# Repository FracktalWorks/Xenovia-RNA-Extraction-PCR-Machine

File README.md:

# Xenovia RT-PCR Machine

Ankit Bhatnagar
ankit.bhatnagarindia@gmail.com

Vijay Raghav Varada
vjvarada@fracktal.in

## Firmware Architecture

## Firmware Functional Block Diagram

* `main_window` in main.py is an object of `MainUI` class that is the workhorse for the firmware.
* `MainUI` class is the main workhorse. Using getter methods the `Printer` class and `Tests` class is parsed into the `MainUI` class. `xenovia.ui` is inherited by `MainUI` class.
* `xenovia_ui` is the generated code from the `xenovia_ui.ui` file made in Qt Designer and then converted into python code using PyQt5 UI code generator 5.14.2 .
* `Printer` class abstracts the Gcode calls to the control board connected over USB and presents an API that is used by `tests` and `MainUI` etc for printer movement functionality.
* `MKSCheck` creates the connection to the printer over USB.
* `MKSSerialCommunication` class handles the communication to the printer. It's initialised by the `Printer` class.
* `Tests` is the class that manages available tests, listing them, parsing their class object to `MainUI` etc.
* tests folder contains the assays which are dynamically initialised into `MainUI` by `Tests` class. Each Assay class inherits `TestBase` class.
* `TestBase` contains methods common to all Assays.
* When an assay class in dynamically created into `MainUI` by `Tests`, the base function movement classes of `Pipette`, `TipTrash`, `Magnet` etc which have motion related medhods are passed into it.
* `MechanicalParameters` has all the dimensions of the accessories in the machine, that the base function movement classes of `Pipette`, `TipTrash`, `Magnet` etc uses.

### Research Links:

## Xenovia Color Sensor 

### Main Components:
1. veml6040 colour sensor IC:  [Datasheet](https://www.vishay.com/docs/84276/veml6040.pdf)
2. TCA9548A I2C Switch: [Datasheet](https://www.ti.com/lit/ds/symlink/tca9548a.pdf)

### Research Links for interfacing:
1. Functionality and example application of TCA9548A [link](https://www.hackster.io/tarantula3/tca9548a-i2c-multiplexer-module-with-arduino-and-nodemcu-3d3313)
2. VEML6040 python example code [link](https://www.raspberrypi.org/forums/viewtopic.php?t=263498)
3. To test detection from raspberry pi and basic understanding of TCA9548A [link](https://www.raspberrypi.org/forums/viewtopic.php?t=146416)
4. Raspberry Pi I2C interfacing Tutorial, detecting connected hardware [link](https://learn.adafruit.com/adafruits-raspberry-pi-lesson-4-gpio-setup/configuring-i2c)
5. SMBus [link](http://wiki.erazor-zone.de/wiki:linux:python:smbus:doc)
### Degugging and Bugs:
#### Hardware:
V1.4
1. Upstream SDA SCL lines on the TCA9548A does not have pullup resistors, uses internal pullups on the raspberry pi board
2. Diodes on the Raspberry Pi shield need to be reversed due to error in placement from JLCPCB

#### Software:

1. Reset pin on Raspberry Pi is low by default, change to high to prevent resetting the TCA9548A or just disconnect the reset pin.

## Xenovia Application Auto Startup References

### X Server + Xenovia Application Autostart
1. https://www.raspberrypi.org/forums/viewtopic.php?t=42888
2. https://www.websences.com/dpkg-reconfigure-x11-common/
3. https://github.com/raspberrypi/linux/issues/2517#issuecomment-387867933

1. global xinitrc file : /etc/X11/xinit/xinitrc (set permissin a+x)
2. pi user .xinitrc file : /home/pi/.xinitrc (set permission a+x)
3. global rc.local file : /etc/rc.local (set permission a+x)

### Removing Logo And Initial Boot Stuff

1. https://www.raspberrypi.org/forums/viewtopic.php?t=189666
2. https://www.raspberrypi.org/forums/viewtopic.php?t=236647
3. https://www.thedigitalpictureframe.com/customize-your-raspberry-pi-splash-screen-raspbian-stretch-april-2019-version/
4. https://github.com/raspberrypi/linux/issues/2517#issuecomment-3878679334
5. https://raspberrypi.stackexchange.com/questions/59310/remove-boot-messages-all-text-in-jessie

### Execution Flow
```rc.local ---> startx ---> global .xinitrc ---> pi user .xinitrc ---> xenovia program```

### Assay
For the assay instructions, 
refer https://docs.google.com/spreadsheets/d/1H6HLvYigPT_AyQD-u33ocX8Hzw2NfqiJH0Qfa-5BsPY/edit?usp=sharing

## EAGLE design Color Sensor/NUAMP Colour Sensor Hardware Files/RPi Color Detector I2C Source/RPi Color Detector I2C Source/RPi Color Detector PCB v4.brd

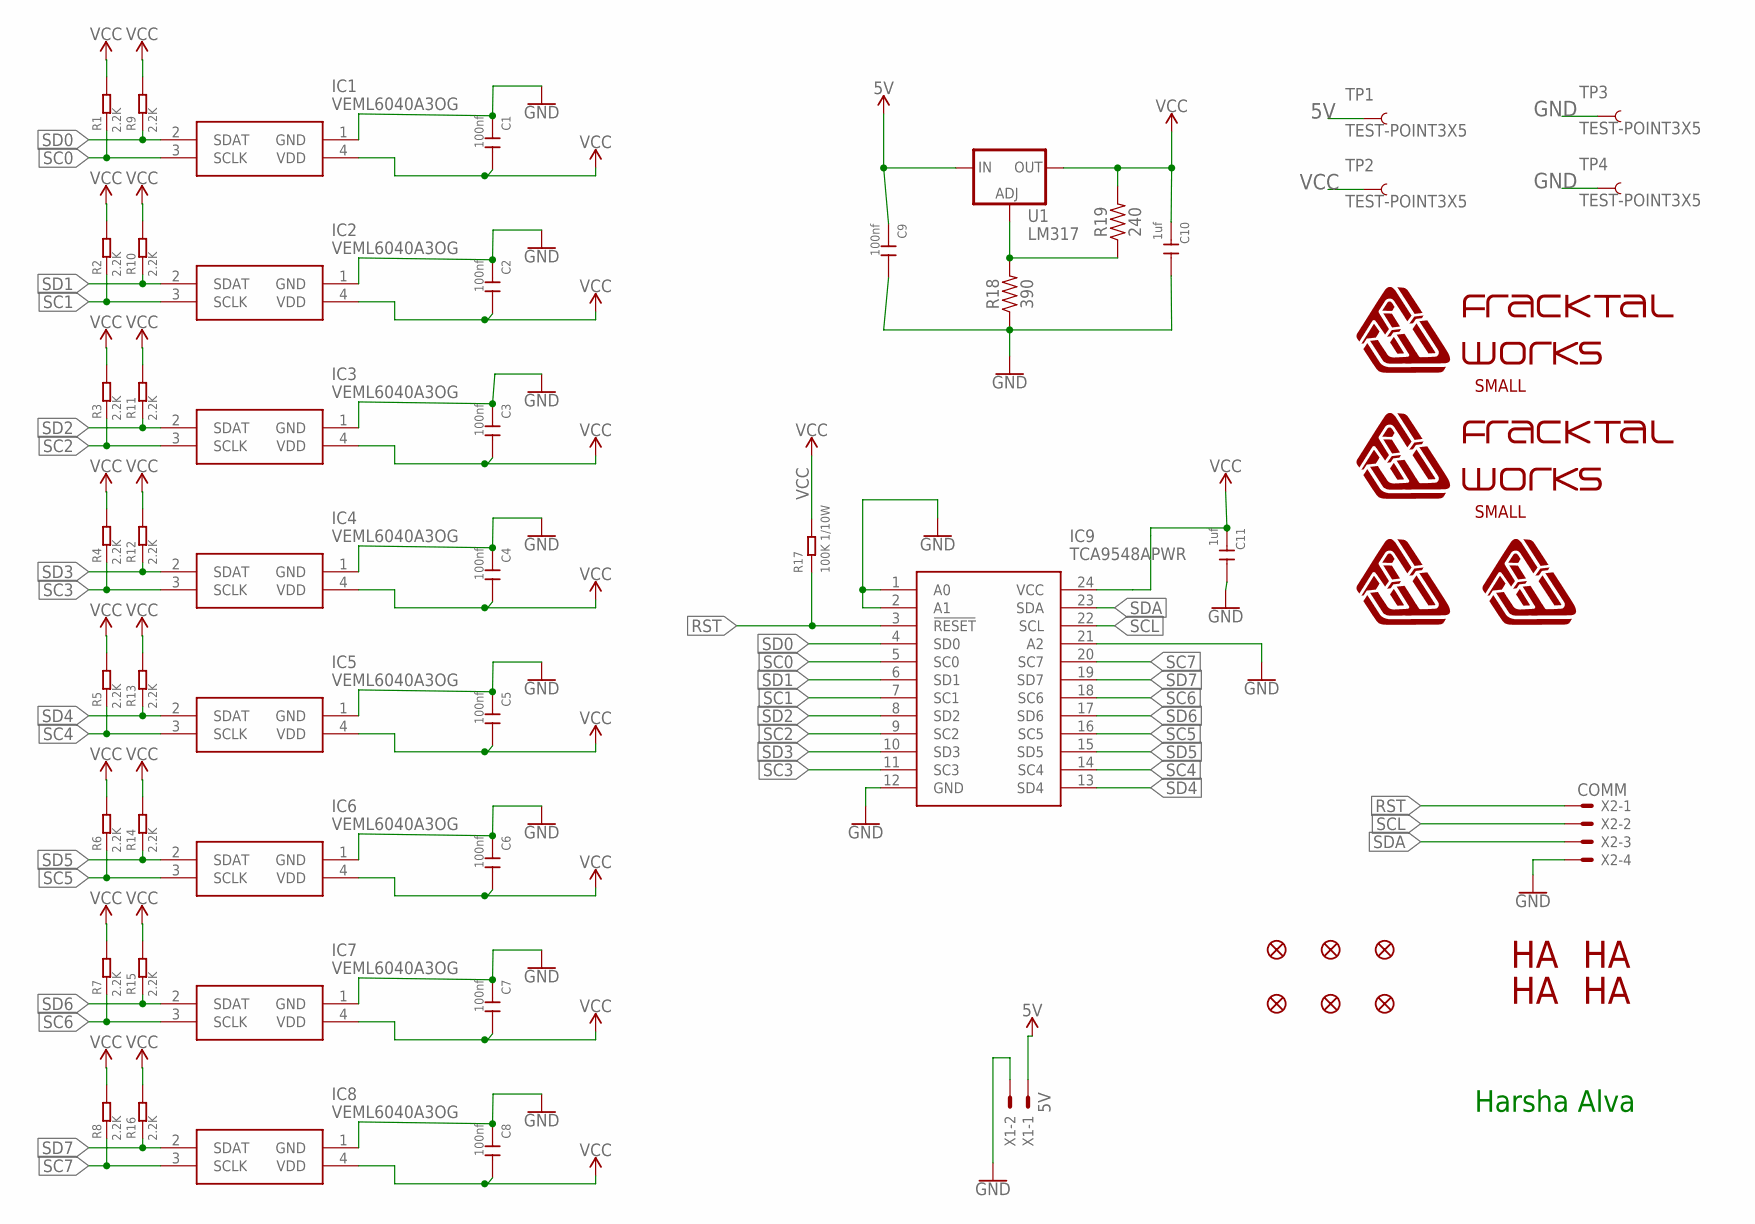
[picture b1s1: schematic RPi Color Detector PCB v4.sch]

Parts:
C1, C2, C3, C4, C5, C6, C7, C8, C9: 100nf; C0402
C10, C11: 1uf; C0402
FD1, FD2, FD3, FD4, FD5, FD6: FIDUCIAL1X2; FIDUCIAL-1X2
FWLOGO_1, FWLOGO_2: FWLOGO
FW_TXT_S_1, FW_TXT_S_2: FWLOGO_TEXT_SMALL
IC1, IC2, IC3, IC4, IC5, IC6, IC7, IC8: VEML6040A3OG
IC9: TCA9548APWR; SOP65P640X120-24N
M_HA_1, M_HA_2, M_HA_3, M_HA_4: HA_MARK
R1, R2, R3, R4, R5, R6, R7, R8, R9, R10, R11, R12, R13, R14, R15, R16: 2.2K; R0603
R17: 100K 1/10W; R0603
R18: 390; 0603
R19: 240; 0603
TP1, TP2, TP3, TP4: TEST-POINT3X5; PAD.03X.05
U1: LM317; SOT223
X1: 5V; JST-XH-02-PACKAGE-LONG-PAD
X2: COMM; JST-XH-04-PACKAGE-ROUND-PAD

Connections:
5V: C9.1, TP1.P$1, U1.3 (IN), X1.1
ADJ: R18.2, R19.1, U1.1 (ADJ)
GND: C1.1, C2.1, C3.1, C4.1, C5.1, C6.1, C7.1, C8.1, C9.2, C10.2, C11.2, IC1.1 (GND), IC2.1 (GND), IC3.1 (GND), IC4.1 (GND), IC5.1 (GND), IC6.1 (GND), IC7.1 (GND), IC8.1 (GND), IC9.1 (A0), IC9.2 (A1), IC9.12 (GND), IC9.21 (A2), R18.1, TP3.P$1, TP4.P$1, X1.2, X2.4
RST: IC9.3 (!RESET), R17.1, X2.1
SC0: IC1.3 (SCLK), IC9.5 (SC0), R1.1
SC1: IC2.3 (SCLK), IC9.7 (SC1), R2.1
SC2: IC3.3 (SCLK), IC9.9 (SC2), R3.1
SC3: IC4.3 (SCLK), IC9.11 (SC3), R4.1
SC4: IC5.3 (SCLK), IC9.14 (SC4), R5.1
SC5: IC6.3 (SCLK), IC9.16 (SC5), R6.1
SC6: IC7.3 (SCLK), IC9.18 (SC6), R7.1
SC7: IC8.3 (SCLK), IC9.20 (SC7), R8.1
SCL: IC9.22 (SCL), X2.2
SD0: IC1.2 (SDAT), IC9.4 (SD0), R9.1
SD1: IC2.2 (SDAT), IC9.6 (SD1), R10.1
SD2: IC3.2 (SDAT), IC9.8 (SD2), R11.1
SD3: IC4.2 (SDAT), IC9.10 (SD3), R12.1
SD4: IC5.2 (SDAT), IC9.13 (SD4), R13.1
SD5: IC6.2 (SDAT), IC9.15 (SD5), R14.1
SD6: IC7.2 (SDAT), IC9.17 (SD6), R15.1
SD7: IC8.2 (SDAT), IC9.19 (SD7), R16.1
SDA: IC9.23 (SDA), X2.3
VCC: C1.2, C2.2, C3.2, C4.2, C5.2, C6.2, C7.2, C8.2, C10.1, C11.1, IC1.4 (VDD), IC2.4 (VDD), IC3.4 (VDD), IC4.4 (VDD), IC5.4 (VDD), IC6.4 (VDD), IC7.4 (VDD), IC8.4 (VDD), IC9.24 (VCC), R1.2, R2.2, R3.2, R4.2, R5.2, R6.2, R7.2, R8.2, R9.2, R10.2, R11.2, R12.2, R13.2, R14.2, R15.2, R16.2, R17.2, R19.2, TP2.P$1, U1.2 (OUT)

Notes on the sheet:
Harsha Alva

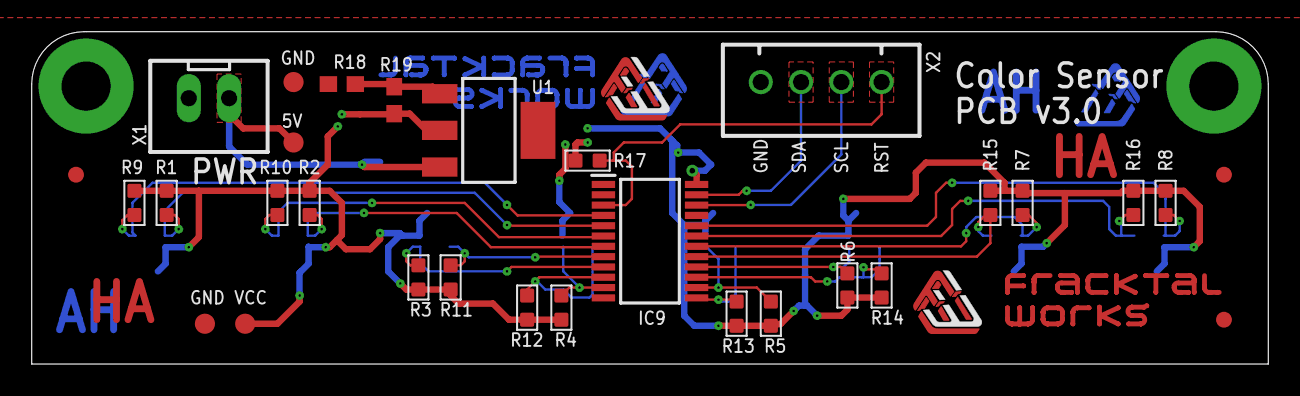
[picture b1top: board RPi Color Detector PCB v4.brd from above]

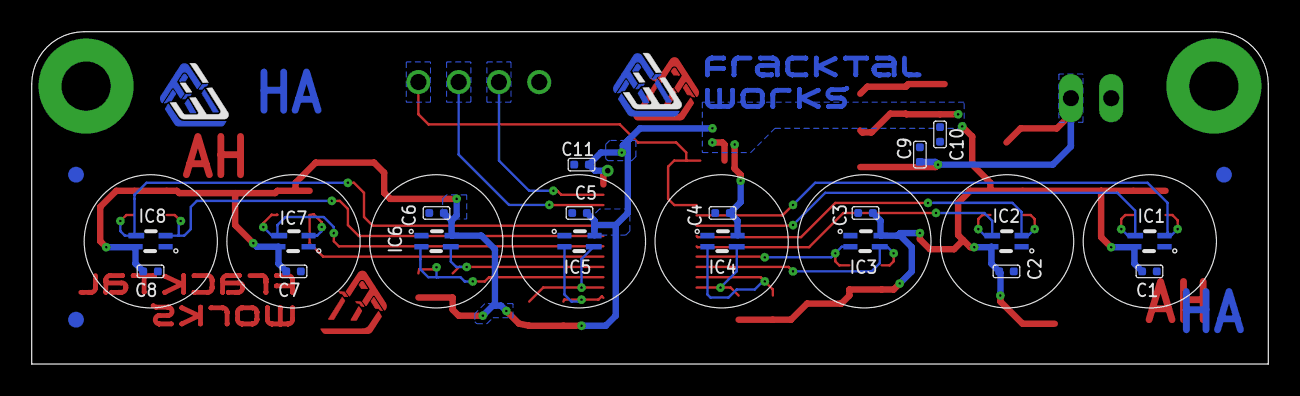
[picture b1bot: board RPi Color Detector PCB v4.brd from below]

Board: 2 copper layers, 78.0 x 21.0 mm, 60 parts (26 on the bottom side), 23 nets.

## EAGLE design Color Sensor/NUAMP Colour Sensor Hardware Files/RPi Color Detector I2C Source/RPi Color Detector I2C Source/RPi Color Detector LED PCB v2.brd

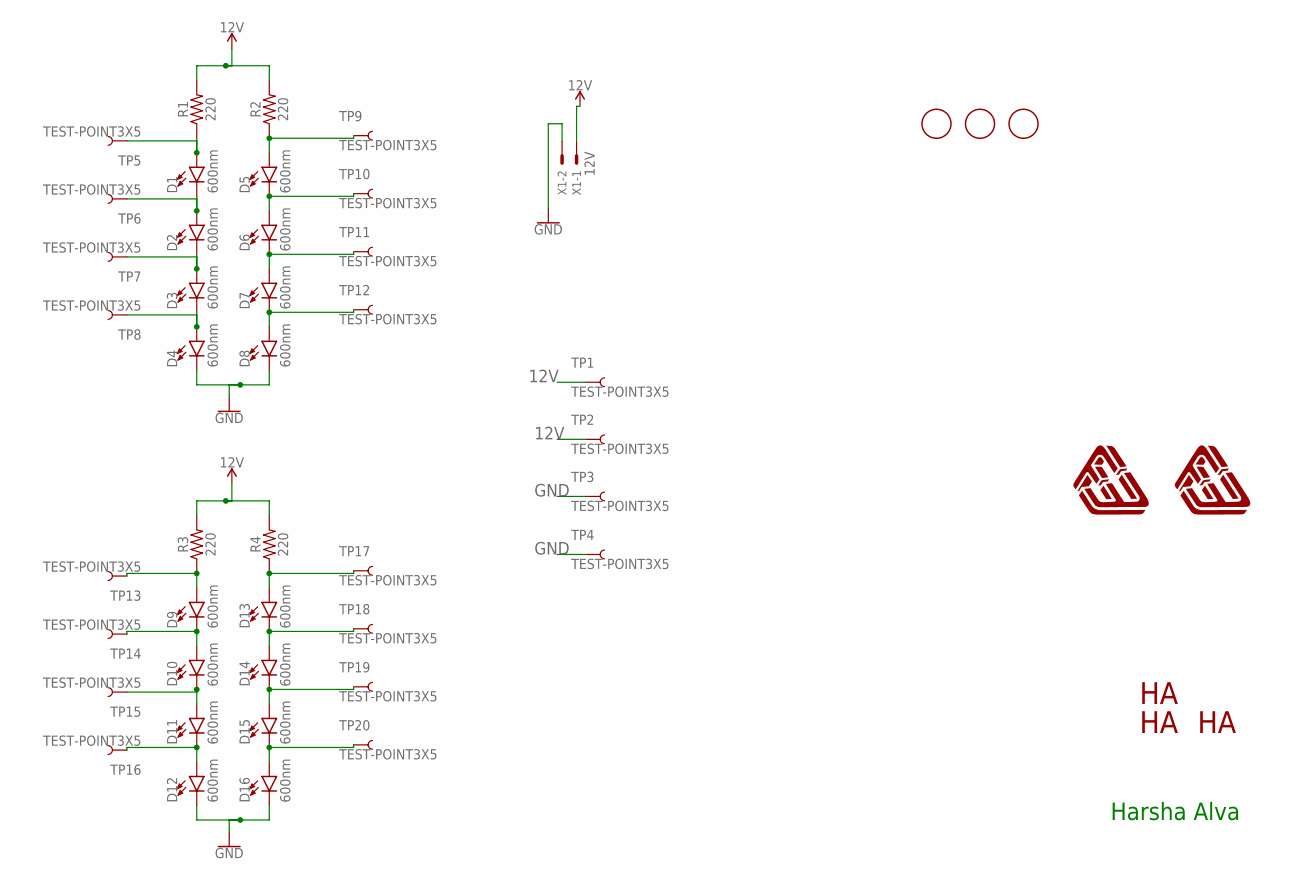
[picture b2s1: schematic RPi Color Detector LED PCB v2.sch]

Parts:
D1, D2, D3, D4, D5, D6, D7, D8, D9, D10, D11, D12, D13, D14, D15, D16: 600nm; LED-0603
FWLOGO_1, FWLOGO_2: FWLOGO
M_HA_1, M_HA_3, M_HA_4: HA_MARK
R1, R2, R3, R4: 220; 0603
TP1, TP2, TP3, TP4, TP5, TP6, TP7, TP8, TP9, TP10, TP11, TP12, TP13, TP14, TP15, TP16, TP17, TP18, TP19, TP20: TEST-POINT3X5; PAD.03X.05
U$1, U$2, U$3: FIDUCIAL; FIDUCIAL_1MM
X1: 12V; JST-XH-02-PACKAGE-LONG-PAD

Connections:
12V: R1.2, R2.2, R3.2, R4.2, TP1.P$1, TP2.P$1, X1.1
GND: D4.C, D8.C, D12.C, D16.C, TP3.P$1, TP4.P$1, X1.2
unnamed: D1.A, R1.1, TP5.P$1
unnamed: D1.C, D2.A, TP6.P$1
unnamed: D2.C, D3.A, TP7.P$1
unnamed: D3.C, D4.A, TP8.P$1
unnamed: D5.A, R2.1, TP9.P$1
unnamed: D5.C, D6.A, TP10.P$1
unnamed: D6.C, D7.A, TP11.P$1
unnamed: D7.C, D8.A, TP12.P$1
unnamed: D9.A, R3.1, TP13.P$1
unnamed: D9.C, D10.A, TP14.P$1
unnamed: D10.C, D11.A, TP15.P$1
unnamed: D11.C, D12.A, TP16.P$1
unnamed: D13.A, R4.1, TP17.P$1
unnamed: D13.C, D14.A, TP18.P$1
unnamed: D14.C, D15.A, TP19.P$1
unnamed: D15.C, D16.A, TP20.P$1

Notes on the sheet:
Harsha Alva

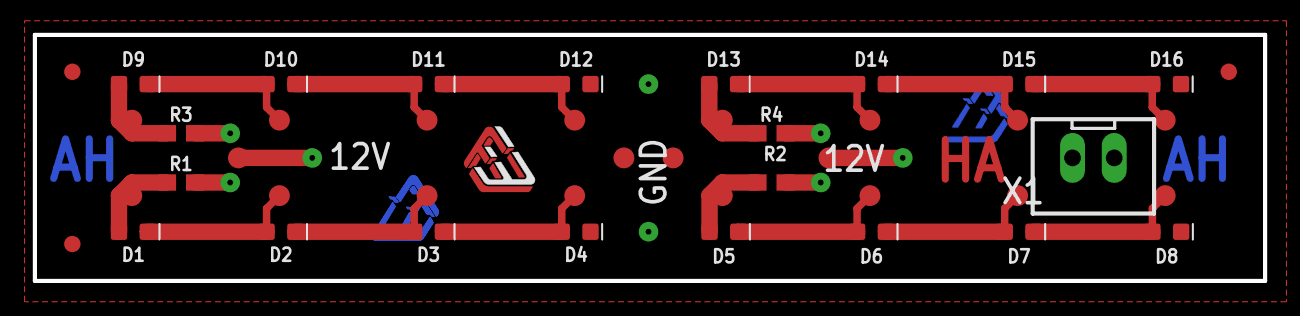
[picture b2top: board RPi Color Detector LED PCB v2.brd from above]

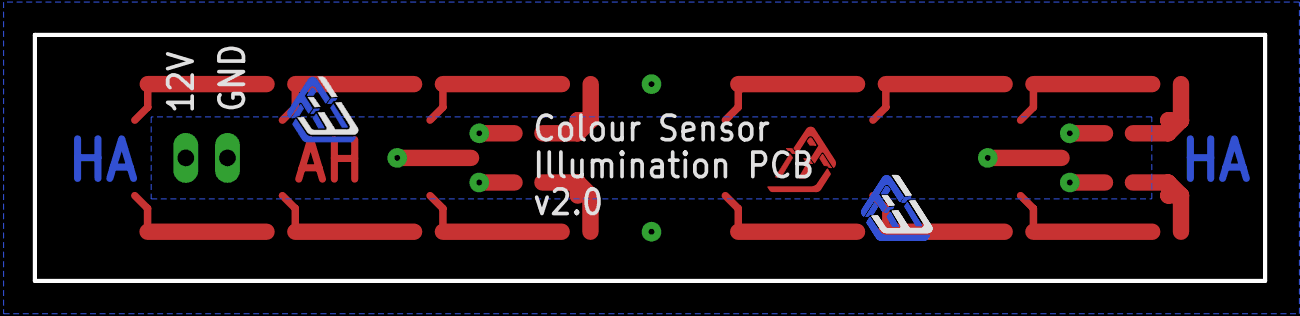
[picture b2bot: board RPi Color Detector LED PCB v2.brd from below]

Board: 2 copper layers, 75.0 x 15.0 mm, 51 parts (5 on the bottom side), 18 nets.

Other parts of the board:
FWLOGO_4, FWLOGO_5: FWLOGO

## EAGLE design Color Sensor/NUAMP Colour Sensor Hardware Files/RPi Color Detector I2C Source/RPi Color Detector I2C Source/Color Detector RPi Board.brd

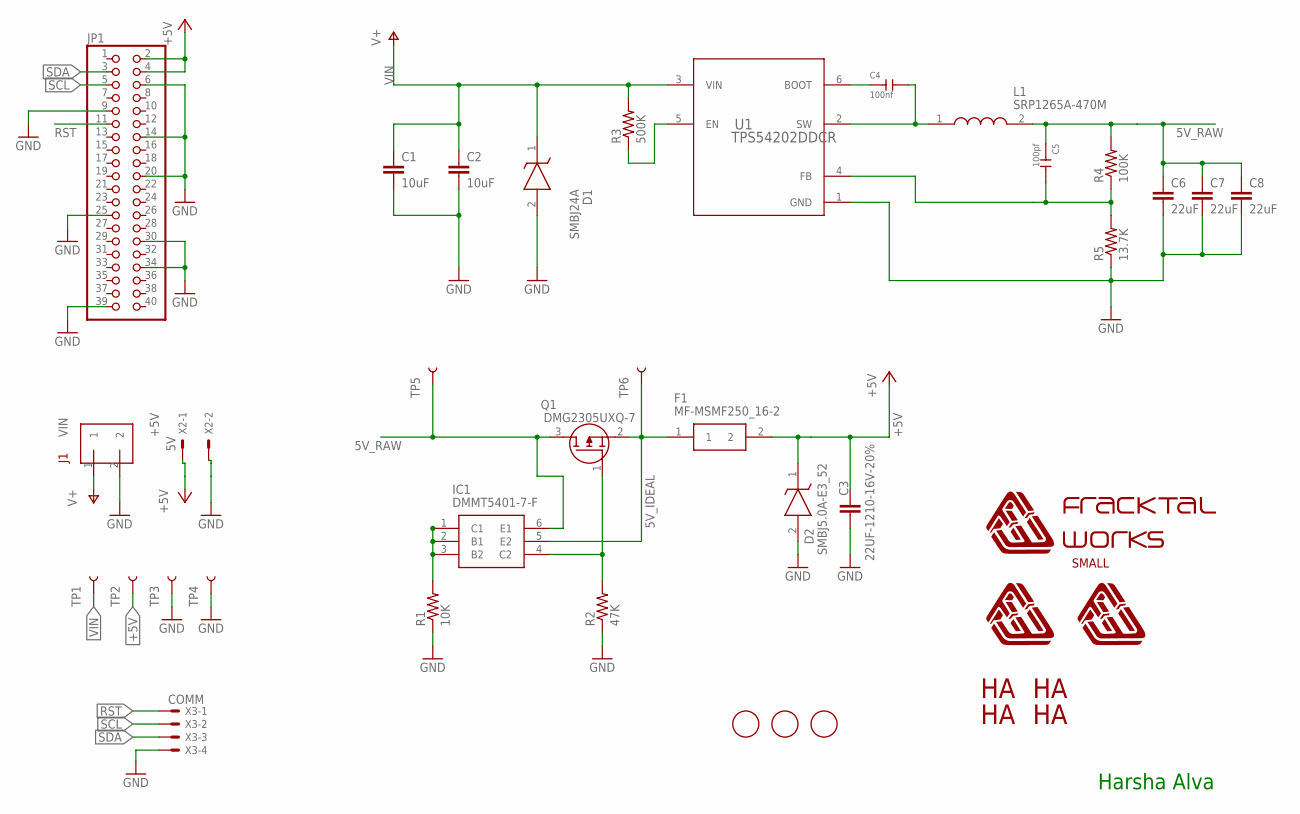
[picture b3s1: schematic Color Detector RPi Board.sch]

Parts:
$1_39_$_2020-06-29_16-08-13, $1_40_$_2020-06-29_16-08-1, $1_40_$_2020-06-29_16-08-13: HA_MARK
C1, C2: 10uF; 1210
C3: 22UF-1210-16V-20%; 1210
C4: 100nf; C0603
C5: 100pf; C0603
C6, C7, C8: 22uF; 1210
D1: SMBJ24A; DIOM5436X244N
D2: SMBJ5.0A-E3_52; DIOM5436X244N
F1: MF-MSMF250_16-2; FUSC4632X160N
FWLOGO_1, FWLOGO_2: FWLOGO
FW_TXT_S_2: FWLOGO_TEXT_SMALL
IC1: DMMT5401-7-F; SOT95P275X110-6N
J1: TERMINALBLOCK/TOYO/2PIN/5MMPITCH
JP1: RASPBERRYPI_3B_GPIO
L1: SRP1265A-470M; SRP1265A
M_HA_1: HA_MARK
Q1: DMG2305UXQ-7; SOT96P240X110-3N
R1: 10K; M0805
R2: 47K; M0805
R3: 500K; R0603
R4: 100K; R0603
R5: 13.7K; R0603
TP1, TP2, TP3, TP4, TP5, TP6: TEST-POINT3X5; PAD.03X.05
U1: TPS54202DDCR; DDC0006A_N
U$1, U$2, U$3: FIDUCIAL; FIDUCIAL_1MM
X2: 5V; JST-XH-02-PACKAGE-LONG-PAD
X3: COMM; JST-XH-04-PACKAGE-ROUND-PAD

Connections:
5V_IDEAL: F1.1, IC1.5 (E2), Q1.2 (S), TP6.P$1
5V_RAW: C5.1, C6.1, C7.1, C8.1, IC1.6 (E1), L1.2, Q1.3 (D), R4.2, TP5.P$1
+5V: C3.2, D2.1 (K), F1.2, JP1.2, JP1.4, TP2.P$1, X2.1
GND: C1.2, C2.2, C3.1, C6.2, C7.2, C8.2, D1.2 (A), D2.2 (A), J1.2, JP1.6, JP1.9, JP1.14, JP1.20, JP1.25, JP1.30, JP1.34, JP1.39, R1.1, R2.1, R5.1, TP3.P$1, TP4.P$1, U1.1 (GND), X2.2, X3.4
unnamed: IC1.4 (C2), Q1.1 (G), R2.2
unnamed: IC1.1 (C1), IC1.2 (B1), IC1.3 (B2), R1.2
unnamed: R3.1, U1.5 (EN)
unnamed: C5.2, R4.1, R5.2, U1.4 (FB)
unnamed: C4.2, L1.1, U1.2 (SW)
unnamed: C4.1, U1.6 (BOOT)
RST: JP1.11, X3.1
SCL: JP1.5, X3.2
SDA: JP1.3, X3.3
VIN: C1.1, C2.1, D1.1 (K), J1.1, R3.2, TP1.P$1, U1.3 (VIN)

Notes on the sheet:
Harsha Alva

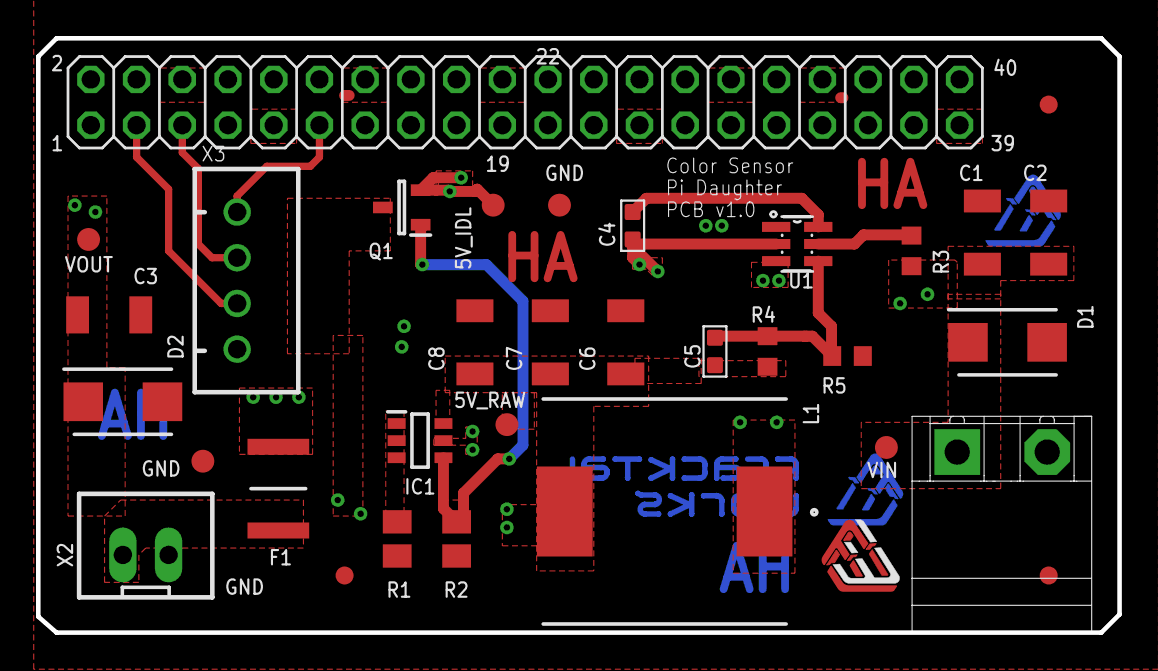
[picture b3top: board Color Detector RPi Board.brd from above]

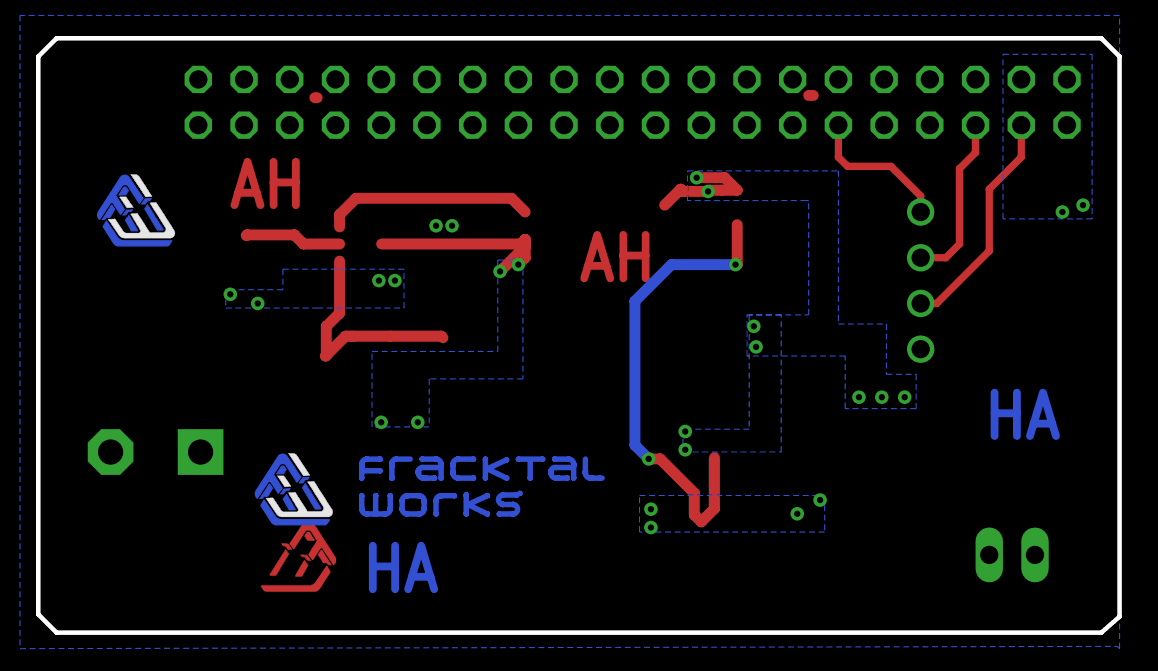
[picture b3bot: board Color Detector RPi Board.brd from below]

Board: 2 copper layers, 60.1 x 33.0 mm, 40 parts (4 on the bottom side), 14 nets.

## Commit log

2020-10-19 added readme
2020-10-19 added HW architecture
2020-10-19 added HW diagram
2020-10-19 made mux class
2020-10-21 cleaned up code, created colorSesnor class
2020-10-22 updated code with minor assertions and doccumentation
2020-10-27 added xenovia main files
2020-10-27 Initial
    Initial
2020-10-28 Xenovia folder code to be used
    Includes new code change to take value of feedrates on assay execution.
2020-10-28 Includes new code change to take value of feedrates on assay execution. RnD
    Includes new code change to take value of feedrates on assay execution.
    RnD
    OLD code deleted
2020-10-28 edited doccumentation
2020-10-28 changed mane of folder to xenovia
2020-10-29 added code functional block diagram to doccumentation
2020-10-29 added functional block diagram to readme.md
2020-10-29 made changes to accomadate PCR Tray
2020-10-29 Revert "made changes to accomadate PCR Tray"
    This reverts commit 22687f552e389f6cc751df335eb4efd658d00193.
2020-10-29 Revert
    Revert
2020-10-31 changed stylesheet for tests
2020-10-31 changed stylesheet for tests, added moveToTrash() method
2020-10-31 cleanup
2020-10-31 updated doccumention
2020-10-31 Updated TestCovid19.py
    Updated TestCovid19.py
    _Assay for RNA Isolation only
2020-10-31 fixed bug with button
2020-10-31 Update Pipette.py
    Update Pipette.py
    Volume levels. Yet to be calibrated.
2020-10-31 changed button color
2020-11-05 bypassed patient data screen
2020-11-05 New build mechanically
    Changed major co-ordinates of removable parts.
    Tip trash code is also changed
2020-11-05 Update MechanicalParameters.py
    Few more MechanicalParameters update
2020-11-09 Update README.md
    Updated removal of boot messages
2020-11-09 added boot screen
2020-11-10 chanegd move to trash function
2020-11-11 Changes
    Mechanical Paramenters changed
    1. Magnet reworked
    2. Goto trash to be worked.
2020-11-12 Changes on mechanical parameters and added moveUp and moveToTrashUnlock
    1. moveUp
    2. moveToTrashUnlock
    3. COVID 19 on testing .
2020-11-12 added move servo when machine starts up and on VTM screen
2020-11-12 modified homing with servo
2020-11-12 COVID19 updates
    COVID19 updates
2020-11-17 Update README.md
    Edited some grammatical mistakes and no other changes were made.
2020-11-19 Made changes on COVID19 test
    Made Assay changes to 16 samples test. Previously it was 32 sample test for RNA extraction.
2020-11-26 --
    --
2021-01-02 Build with magnets under the well tray
    Hardware change
    1. Magnets slide up and down with servo P0 with change in stroke- angle to 125
2021-01-09 Offset distance in well tray changed
    Offset distance in well tray changed
2021-04-05 05042021
2021-04-05 -
    -

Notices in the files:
parts and their libraries:
SparkFun-Connectors: Licensing: Creative Commons ShareAlike 4.0 International - https://creativecommons.org/licenses/by-sa/4.0
SparkFun-Connectors: Licensing: CC v3.0 Share-Alike You are welcome to use this library for commercial purposes.
